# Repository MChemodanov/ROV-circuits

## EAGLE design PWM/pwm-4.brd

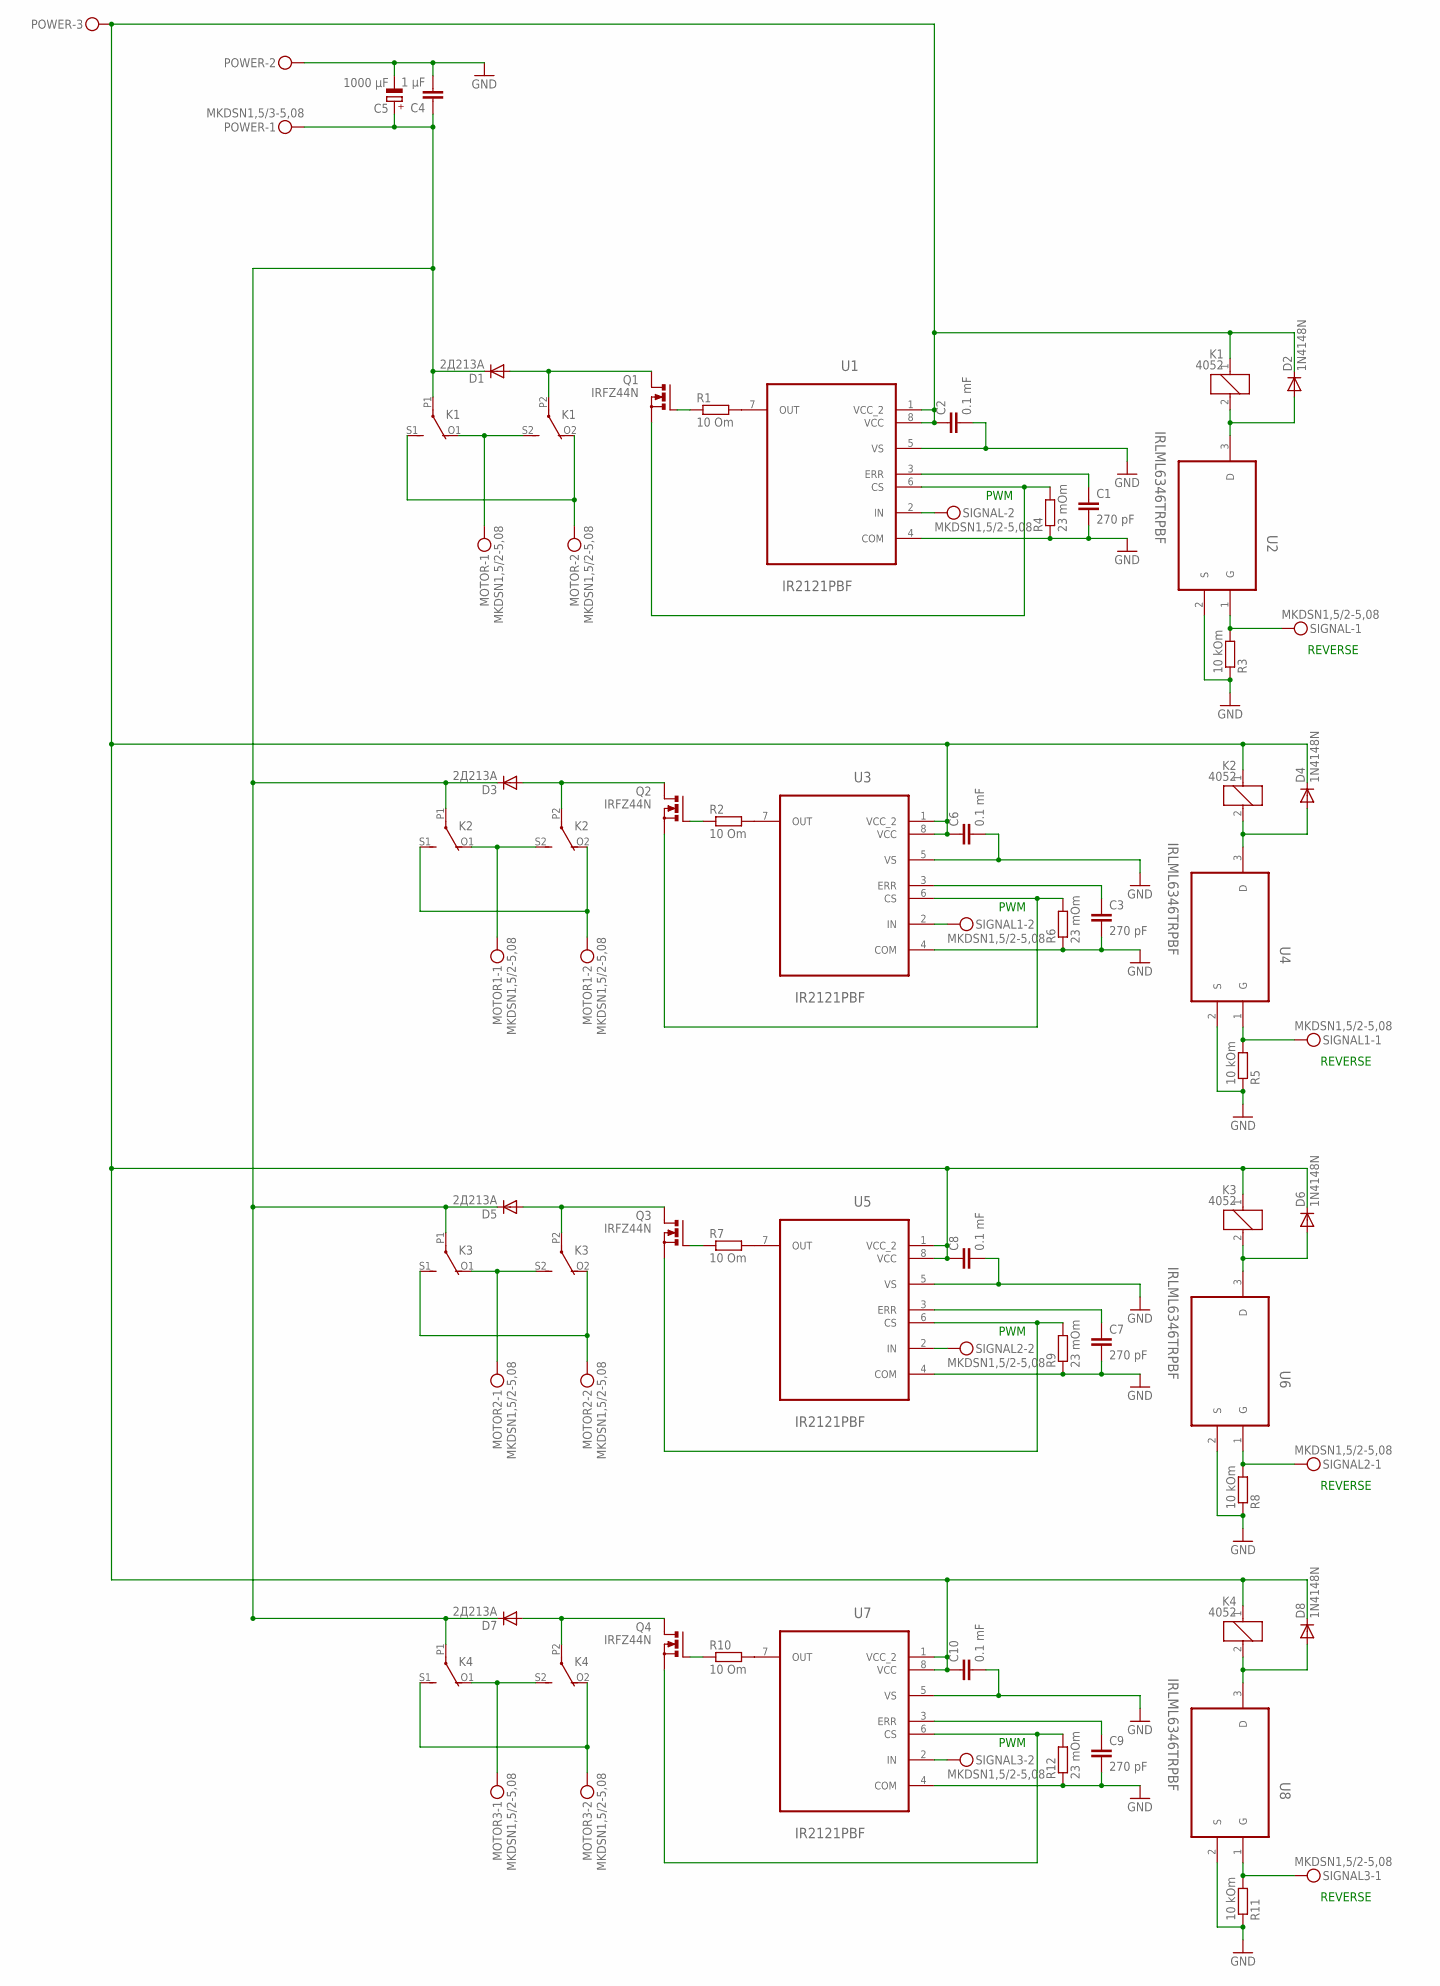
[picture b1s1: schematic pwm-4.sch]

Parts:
C1, C3, C7, C9: 270 pF; C025-025X050
C2, C6, C8, C10: 0.1 mF; C025-025X050
C4: 1 µF; C2.5-3
C5: 1000 µF; E7,5-18
D1, D3, D5, D7: 2Д213А; C1702-05
D2, D4, D6, D8: 1N4148N; D-2.5
K1, K2, K3, K4: 4052; F4052
MOTOR, MOTOR1, MOTOR2, MOTOR3: MKDSN1,5/2-5,08
POWER: MKDSN1,5/3-5,08
Q1, Q2, Q3, Q4: IRFZ44N; TO220BV
R1, R2, R7, R10: 10 Om; 0204/5
R3, R5, R8, R11: 10 kOm; 0204/5
R4, R6, R9, R12: 23 mOm; 0204/5
SIGNAL, SIGNAL1, SIGNAL2, SIGNAL3: MKDSN1,5/2-5,08
U1, U3, U5, U7: IR2121PBF; DIP254P762X533-8
U2, U4, U6, U8: IRLML6346TRPBF; SOT95P240X112-3N

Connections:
GND: C1.2, C2.2, C3.2, C4.2, C5.-, C6.2, C7.2, C8.2, C9.2, C10.2, POWER.2, R3.1, R4.1, R5.1, R6.1, R8.1, R9.1, R11.1, R12.1, U1.4 (COM), U1.5 (VS), U2.2 (S), U3.4 (COM), U3.5 (VS), U4.2 (S), U5.4 (COM), U5.5 (VS), U6.2 (S), U7.4 (COM), U7.5 (VS), U8.2 (S)
unnamed: SIGNAL.2, U1.2 (IN)
unnamed: R3.2, SIGNAL.1, U2.1 (G)
unnamed: K1.O1 (O), K1.S2 (S), MOTOR.1
unnamed: K1.O2 (O), K1.S1 (S), MOTOR.2
unnamed: D1.A, K1.P2, Q1.D
unnamed: C1.1, U1.3 (ERR)
unnamed: D2.A, K1.2, U2.3 (D)
unnamed: C4.1, C5.+, D1.C, D3.C, D5.C, D7.C, K1.P1, K2.P1, K3.P1, K4.P1, POWER.1
unnamed: Q1.G, R1.1
unnamed: Q1.S, R4.2, U1.6 (CS)
unnamed: R1.2, U1.7 (OUT)
unnamed: C2.1, C6.1, C8.1, C10.1, D2.C, D4.C, D6.C, D8.C, K1.1, K2.1, K3.1, K4.1, POWER.3, U1.1 (VCC_2), U1.8 (VCC), U3.1 (VCC_2), U3.8 (VCC), U5.1 (VCC_2), U5.8 (VCC), U7.1 (VCC_2), U7.8 (VCC)
unnamed: D4.A, K2.2, U4.3 (D)
unnamed: K2.O2 (O), K2.S1 (S), MOTOR1.2
unnamed: SIGNAL1.2, U3.2 (IN)
unnamed: C3.1, U3.3 (ERR)
unnamed: Q2.S, R6.2, U3.6 (CS)
unnamed: R2.2, U3.7 (OUT)
unnamed: Q2.G, R2.1
unnamed: R5.2, SIGNAL1.1, U4.1 (G)
unnamed: K2.O1 (O), K2.S2 (S), MOTOR1.1
unnamed: D3.A, K2.P2, Q2.D
unnamed: D6.A, K3.2, U6.3 (D)
unnamed: K3.O2 (O), K3.S1 (S), MOTOR2.2
unnamed: SIGNAL2.2, U5.2 (IN)
unnamed: C7.1, U5.3 (ERR)
unnamed: Q3.S, R9.2, U5.6 (CS)
unnamed: R7.2, U5.7 (OUT)
unnamed: Q3.G, R7.1
unnamed: R8.2, SIGNAL2.1, U6.1 (G)
unnamed: K3.O1 (O), K3.S2 (S), MOTOR2.1
unnamed: D5.A, K3.P2, Q3.D
unnamed: D8.A, K4.2, U8.3 (D)
unnamed: K4.O2 (O), K4.S1 (S), MOTOR3.2
unnamed: SIGNAL3.2, U7.2 (IN)
unnamed: C9.1, U7.3 (ERR)
unnamed: Q4.S, R12.2, U7.6 (CS)
unnamed: R10.2, U7.7 (OUT)
unnamed: Q4.G, R10.1
unnamed: R11.2, SIGNAL3.1, U8.1 (G)
unnamed: K4.O1 (O), K4.S2 (S), MOTOR3.1
unnamed: D7.A, K4.P2, Q4.D

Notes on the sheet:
REVERSE
PWM

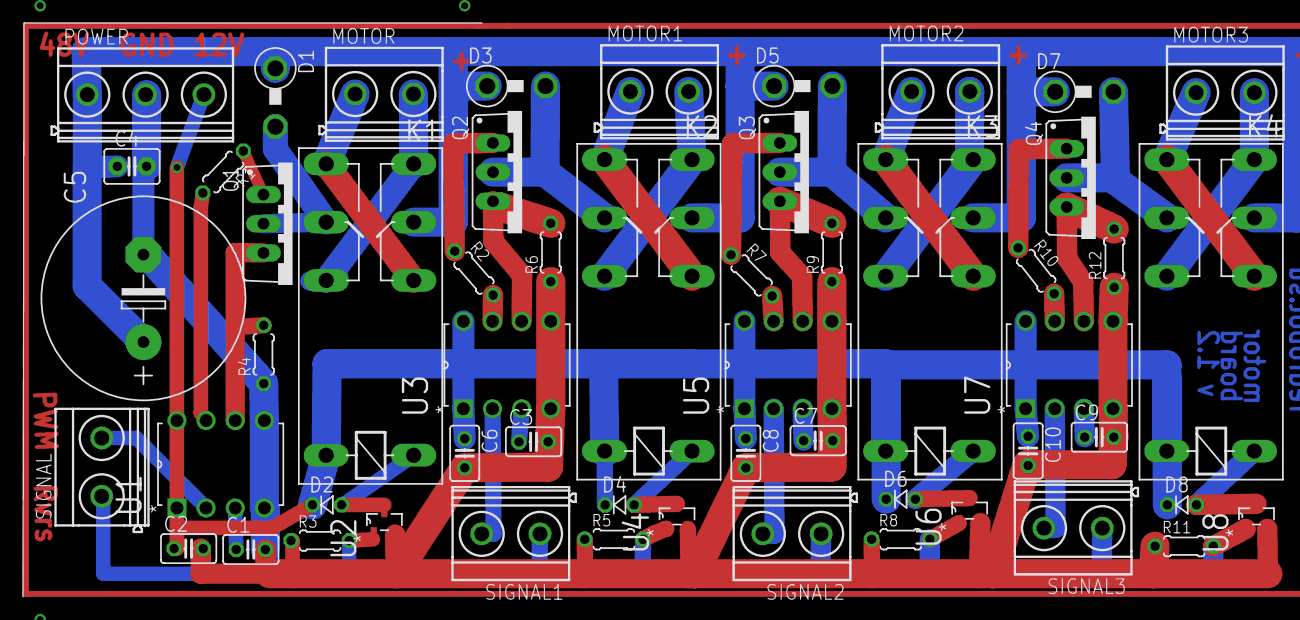
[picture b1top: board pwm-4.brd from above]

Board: 2 copper layers, 55 parts (0 on the bottom side), 43 nets.

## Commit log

2013-12-17 Добавлена схема ШИМ
